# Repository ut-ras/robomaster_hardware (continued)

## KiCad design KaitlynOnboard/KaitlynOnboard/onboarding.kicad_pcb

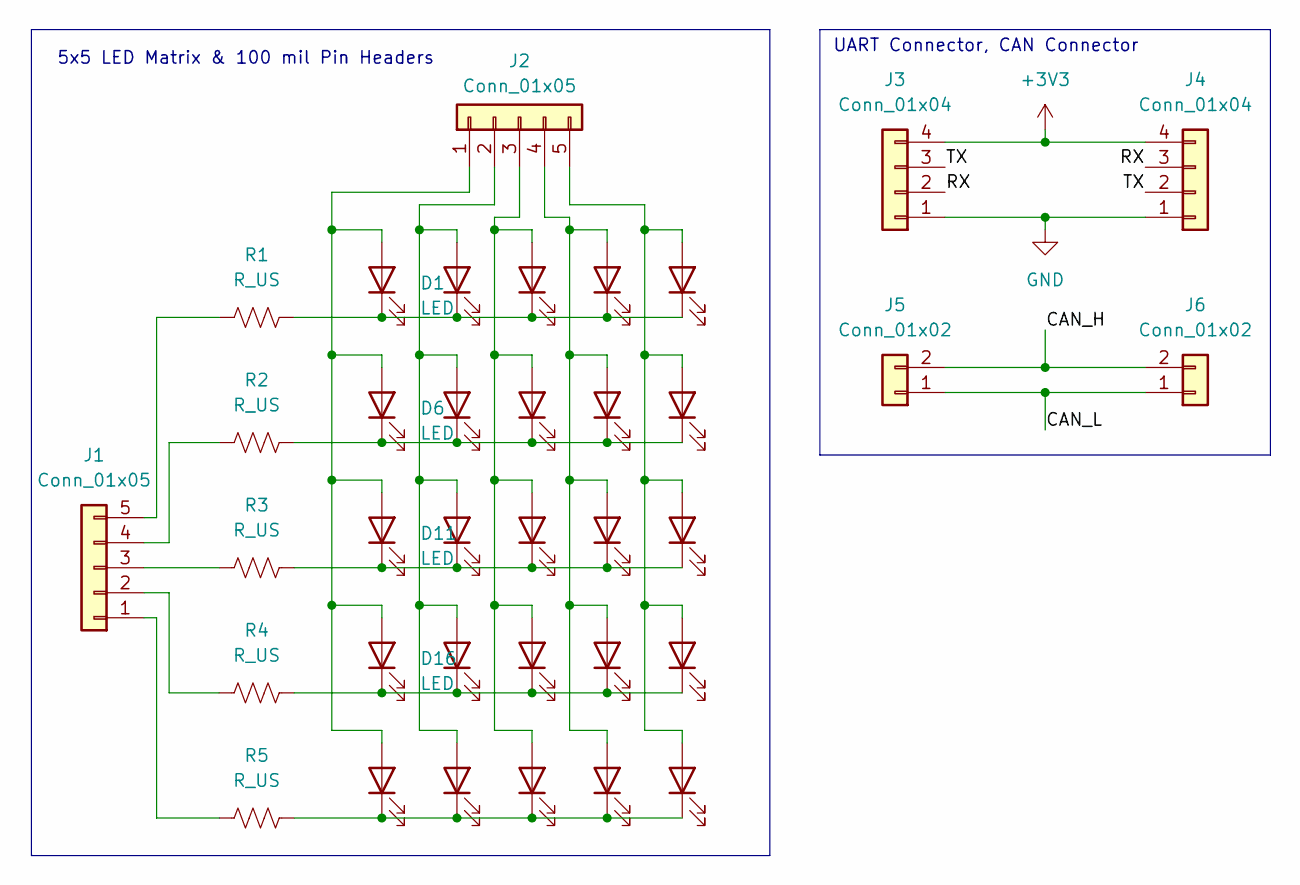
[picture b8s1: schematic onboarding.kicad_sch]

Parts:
D1, D2, D3, D4, D5, D6, D7, D8, D9, D10, D11, D12, D13, D14, D15, D16, D17, D18, D19, D20, D21, D22, D23, D24, D25: LED; LED_D3.0mm
J1, J2: Conn_01x05; PinHeader_1x05_P2.54mm_Vertical
J3, J4: Conn_01x04; JST_GH_BM04B-GHS-TBT_1x04-1MP_P1.25mm_Vertical
J5, J6: Conn_01x02; JST_GH_BM02B-GHS-TBT_1x02-1MP_P1.25mm_Vertical
R1, R2, R3, R4, R5: R_US; R_Axial_DIN0207_L6.3mm_D2.5mm_P7.62mm_Horizontal

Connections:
+3V3: J3.4, J4.4
/CAN_H: J5.2, J6.2
/CAN_L: J5.1, J6.1
/RX: J3.2, J4.3
/TX: J3.3, J4.2
GND: J3.1, J4.1
unnamed: D1.2 (A), D6.2 (A), D11.2 (A), D16.2 (A), D21.2 (A), J2.1
unnamed: D1.1 (K), D2.1 (K), D3.1 (K), D4.1 (K), D5.1 (K), R1.2
unnamed: D5.2 (A), D10.2 (A), D15.2 (A), D20.2 (A), D25.2 (A), J2.5
unnamed: D6.1 (K), D7.1 (K), D8.1 (K), D9.1 (K), D10.1 (K), R2.2
unnamed: D11.1 (K), D12.1 (K), D13.1 (K), D14.1 (K), D15.1 (K), R3.2
unnamed: D2.2 (A), D7.2 (A), D12.2 (A), D17.2 (A), D22.2 (A), J2.2
unnamed: D3.2 (A), D8.2 (A), D13.2 (A), D18.2 (A), D23.2 (A), J2.3
unnamed: D4.2 (A), D9.2 (A), D14.2 (A), D19.2 (A), D24.2 (A), J2.4
unnamed: D16.1 (K), D17.1 (K), D18.1 (K), D19.1 (K), D20.1 (K), R4.2
unnamed: D21.1 (K), D22.1 (K), D23.1 (K), D24.1 (K), D25.1 (K), R5.2
unnamed: J1.1, R5.1
unnamed: J1.2, R4.1
unnamed: J1.3, R3.1
unnamed: J1.4, R2.1
unnamed: J1.5, R1.1

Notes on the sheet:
UART Connector, CAN Connector
5x5 LED Matrix & 100 mil Pin Headers

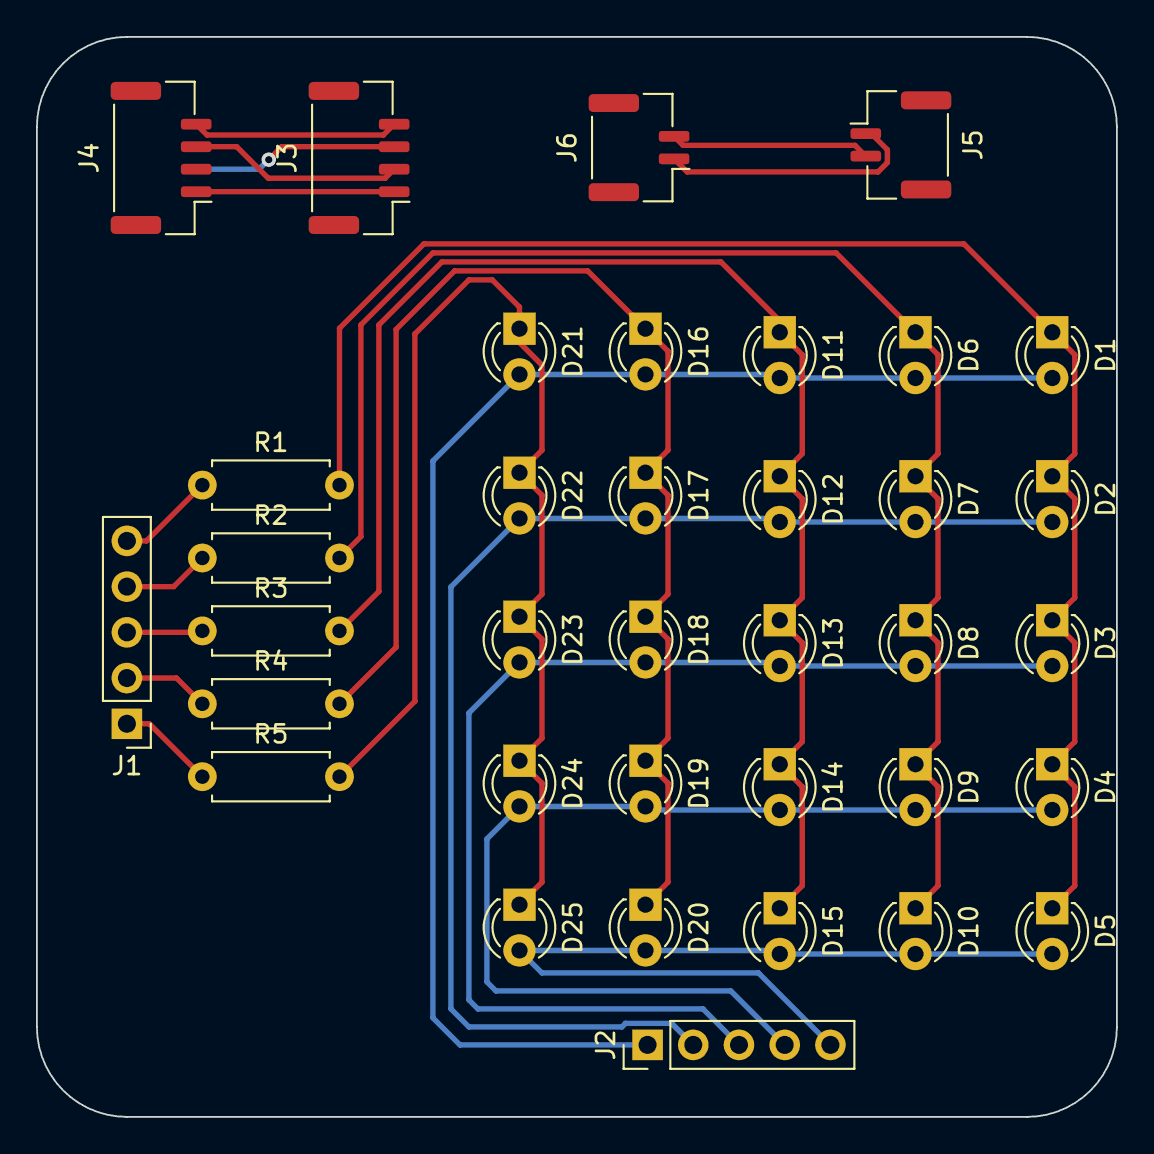
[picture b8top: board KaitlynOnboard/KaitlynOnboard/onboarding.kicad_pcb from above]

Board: 2 copper layers, 60.0 x 60.0 mm, 36 parts (0 on the bottom side), 21 nets.

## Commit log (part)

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2023-09-15 Create a .gitignore for the Chassis project
2023-09-17 Added submodule for Kicad and set libraries
2023-09-17 removed RM library
2023-09-22 Added all connectors + assigned footprints + created PCB file
    Starting layout now
2023-09-23 Change polarity of pins + add circular trace
2023-09-24 Routed CAN lines + made hole octagonal
    + differential pair skew fixed
    Dimensions may be subject to change, will have to redimension and reroute
2023-09-24 Possible indicator method?
2023-09-29 add Turret
2023-09-29 Add gitignore
2023-09-29 Lakshay's method
    I disagree
2023-09-29 Update schematic
2023-09-29 Add pcb
2023-09-30 schematic for dev board
2023-10-14 Added Resistor and LED footprints to schematic
2023-10-14 Wired to connector
2023-10-20 Remove snark
2023-10-21 added power connector
2023-10-22 Completed initial layout
    I'm going to get roasted over some of these choices
2023-10-22 Rearrange parts
2023-10-22 Updated step file
2023-10-22 Add/update READMEs
2023-10-22 Add big boy connector
2023-10-22 Update submodule reference
2023-10-27 Add power connector
    big boy
2023-10-27 Update .STEP file
2023-10-28 Update turret
2023-11-03 Added mounting holes
2023-11-04 Updated PCB to use unified power 6 pin, added 2 1x2 connectors
2023-11-04 Added pour for output
    Will need to add +5V buck + data connector + new power connector
    AAAAAAAAAAAAAAAAAAAAAAA
2023-11-11 Add box to schematic
2023-11-11 reset
2023-11-17 +5V buck
2023-11-18 Pass DRC
2023-11-18 Adjust silkscreen
2023-11-18 Reposition
2023-11-18 Straightened some kinks
2023-11-18 Add random microfit connector
    For data outputs
2023-11-18 Pass JLC DRC
2023-11-18 Mostly finished turret schematic
2023-11-18 Fixed 24V on sabre connector
2023-12-02 began adding traces :p
2023-12-19 Added test points + part number for diode
2023-12-19 update library
2023-12-20 turret dimensions
2024-01-04 Remove unnecessary holes + made some thermal vias into direct pours
2024-01-05 Clear PCB
    Rerouting hajimaruyo
2024-01-06 Much more pleasant dimensions
2024-01-07 Lots of placements
    Big blocks done, time to shuffle them around until I'm happy + route them
    4-layer board in the future?
2024-01-16 Did minor routing
2024-01-20 Winter Break Changes
2024-01-20 added mnfr numbers
2024-01-20 Finished routing
    Turns out we don't need the +5V buck kek
2024-01-27 added gimble power & motor connectors
2024-01-27 Turret change :)
2024-01-27 fixed sizing issues and added diodes
2024-01-27 some things
2024-02-01 Add .STEP file
2024-02-02 Resizing again :D
2024-02-03 made 80x80 & changed to 8 pin connector
2024-02-03 didn't really make any changes b/c of meetings but the board might be too long and I will add connectors to the diodes next time
2024-02-09 02/09/2024 sch
2024-02-10 Changed location of connectors of I2C and added mounting holes. Also I'm currently adding pads for the diodes
2024-02-10 Add files via upload
    WIRES
2024-02-17 Correct voltages
2024-02-17 added power sources
2024-02-17 fixed more sizing issues and I added a 1x4 connector to the data pins
2024-02-23 Fix CAN and change schematic
2024-02-24 Initial layout of footprints on pcb (not final)
2024-02-24 Moved stuff around
    yeah
2024-03-02 layout done need to do ref system
2024-03-02 Adding new ref system, other push now deprecated
2024-03-02 currently fixing footprints and aligned components
2024-03-06 New layout, test points not final
2024-03-06 finishing touches!
2024-03-07 Cleaned up silkscreen
    Went ham ngl
    Also passes all DRC checks
2024-03-08 Added connections to test points, silkscreens need to be renamed.
2024-03-08 J12 silkscreen names
2024-03-09 Hopefully Final DevBoard. I flipped the data connectors and fixed label placement
2024-03-09 forgot to add mounting holes
2024-03-09 Update silkscreen + address Lakshay's concerns
2024-03-09 Tried to fix footprints, also changed to traces for testpoints
2024-03-09 Add another pour
2024-03-18 Update wiring diagram with new proposal
2024-03-18 Create render action
    Getting a little bit silly with automatic rendering so you don't have to open VSCode every time you want to edit this
2024-03-18 Explicit file path
    Should latch onto the file in question now
2024-03-18 Update render.yml
    last try
2024-03-18 Automatically render .drawio files
2024-03-18 Update libraries & changed footprints
2024-03-22 added can2
2024-03-22 Adjust thingamajigs
    2nd CAN, silkscreen
2024-03-22 Adj silk
2024-03-22 Add le pikja
2024-03-22 New CAN Line, cleaned up schematic, changed pcb
2024-03-22 BOMs away
2024-03-23 fixed the tracks and pin headers and I only added diodes to the 3.3V pins
2024-03-23 Change output filtering for the +19V to 0805 (Mouser doesn't have 0603)
2024-03-23 Update footprints + pass DRC
2024-03-23 Add HSS
2024-03-23 Finish watchdog schematic
    idk if it works lol
2024-03-23 Fix power protection + adj silk
2024-03-24 Update and generate IBOM
2024-03-24 Added gerber & drill files, and zip for them
2024-03-24 Rename "plots" to "gerbers"
2024-03-26 Added 3d model
2024-03-29 Changed symbol fields
2024-03-29 added bom
2024-03-29 Add BOM (part 2)
2024-04-01 YEAH
2024-04-01 TEST TO MAKES REU
2024-04-01 just to make sure i don't explode
2024-04-01 UPDATE KICAD LIBRARY TO LATEST COMMIT
2024-04-02 Update README.md
    with Mouser BOM
2024-04-02 Update README.md
    make footer a note
2024-04-27 Assembled all passives
2024-08-14 Update pdf-diff.yml
    PR test
2024-08-14 Update pdf-diff.yml
    to allow for testing
2024-08-14 Update pdf-diff.yml
    upload artifacts => artifact
2024-08-14 Update pdf-diff.yml
    make ${{ github.workspace }}/ explicit
2024-08-14 Update pdf-diff.yml
    copy paste error
2024-08-14 Update pdf-diff.yml
    spel
2024-09-06 Did onboarding!
2024-09-13 Added name to READEME
2024-09-13 finished onboarding edit of readme
2024-09-13 As per Morris's instructions, adding a file with my personal information
2024-09-13 BryanQu test
2024-09-13 raeesahi
2024-09-13 sanjanahai
2024-09-13 message
2024-09-13 i approve of this message
2024-09-13 Hellow World!
2024-09-13 hi :}
2024-09-13 this is a test
2024-09-17 Reorganized chassis, turret, devboard shield, into monorepo
2024-09-17 Renamed directories to match
2024-09-17 Actually change Turret dir name?
2024-09-17 Renamed to Turret directory
2024-09-27 i hope this work
2024-09-27 pls work
2024-09-27 nithinBoarded
2024-09-29 Create SiddharthDtxt
2024-09-29 Update SiddharthDtxt
    Hello!
2024-09-30 New onboarding example
2024-10-01 Create JeffreyK
2024-10-04 added Egan Wang onboarding
2024-10-04 Add files via upload
    Ron Shemmer LED Matrix files
2024-10-04 Andrew onboarding
2024-10-09 new onboarding
2024-10-11 added first set of stuff for electrical diagram
2024-10-11 kicad for armorplate
2024-10-14 Updated ArmorPlate project dir name to be consistent
2024-10-14 onboarding
2024-10-15 Removed extra dir
2024-10-15 Moved some files around
2024-10-18 Prepped Electrical Diagram for meeting
2024-10-18 Initial commit
    Creating project files
2024-10-18 Add schematic page properties
2024-10-20 Added some text in the subsheets to outline what needs to be added inside of each subsheet
2024-10-21 Added two more subsheets and updated all text inside
2024-10-25 Add note about synchronous boost/buck needed
2024-11-09 please work
2024-11-11 Andrew added hierarchical labels to in/out pins on schematic
2024-11-16 added connections for chassis power to supercap
2024-11-16 Completed first version of housekeeping supplies
    +5V and +3V3 from mini PC +24V
2024-11-16 Adjust documentation
2024-11-17 Add encoder board
2024-11-18 Add switch for CW/CCW control
2024-11-23 Added hierarchical labels to ground pins in chassis
2024-11-23 added hierarchial labels for input/output characteristics
2024-11-23 added supercap connection
2024-11-23 Selected components for ideal diode and DACs
2024-11-24 Trying to do current sense but it's not fun
    canercanercnarennc
2024-11-29 Cleaned up hierarchical labels
2024-12-03 Prepped turret sch for 2x8 molex monolithic conn change
2024-12-07 Added hierarchial labels to chassis board, please look over
2024-12-07 separated grounds of powers
2024-12-07 Finish Dev board interface
    sorry morris
2024-12-07 flip
2024-12-07 Fix ground references
2024-12-07 last formatting change I promise
2024-12-07 Update library + update symbols
2024-12-07 Updating symbol library + passing some ERC tests
2024-12-07 Remove previous version of current sense
2024-12-07 Add in voltage control for components
2024-12-07 Added proper peripherals to ideal diode controller
    also updated library
2024-12-08 Finishing buck charger
2024-12-08 Define feedback networks
2024-12-08 Finish up buck
2024-12-08 attempting to fix comparators
    + global routing
2024-12-08 Reannotated
2024-12-15 Adding new DC DC converter IC
2024-12-15 Complete redesign of housekeeping supplies
    Attached picture is for the design of the housekeeping supplies
2025-01-08 Added a 16 input connector
2025-01-27 XT30 outputs to ESCs rotated
2025-01-27 Renamed project files for consistency
2025-01-31 Changed out floating ground connection to its proper counterpart
2025-01-31 Ideating for diff amp
2025-02-01 Created new folder for SPICE simulations, created SPICE simulation for ideal diode controller
2025-02-01 Moving around things
2025-02-03 Finalized Chassis Board
2025-02-07 Added blank project
2025-02-07 Created blank project and added kicad lib changes
2025-02-07 Moved dirs
2025-02-08 not sure :sparkle:
2025-02-08 updated schematic using sp3t switch
2025-02-12 Updated sheet dates & added new subsheets for parts I forgot to include
2025-02-12 Normally open => closed
2025-02-14 Onboarding for Sarthak Sarans
2025-02-15 updated pcb footprint for armorplate
2025-02-15 Replaced buck converter for 3V3, 3V3A, 5V with AZ34063U
2025-02-15 final armorplate pcb with sp3t toggle switch
2025-02-15 Added -3V3
2025-02-15 Added schematic for first stage of boost converter
2025-02-19 Added connector and updated kicad lib
2025-02-21 Updated electrical diagram and Kicad library
2025-02-21 Fixed 16-pin and 8-pin netnames for correct connections, updated gerbers
2025-02-21 Fixed hierachical labels for functionality, naming needs to be changed
2025-02-21 Staged hierarchical changes for chassis, not finished
2025-02-21 fabrication files for armorplate
2025-02-21 gerbfileszip
2025-02-22 started safety discharge
2025-02-22 Changed boost2
2025-02-22 Added starting files for sentry chassis
2025-02-22 Added hierarchical labels
2025-02-22 Updated AND gate input circuits, added specs to diodes
2025-02-22 Replaced opamp with better one
2025-02-28 Update boost 2
2025-03-01 Changed to GNDPWR for -3V3 step-down converter
2025-03-01 Redesigned stage 1 converter for clarity
2025-03-01 sumbission for Neil
2025-03-01 Reduced link size, added buck converter calculations excel sheet
2025-03-07 new boost 2 schematic
2025-03-07 Added hierarchical outputs to chassis grounds
2025-03-07 staging before meeting
2025-03-08 Flip MOSFET for ideal diode controller
2025-03-08 Added internal connection for ref ports and distiniguished i/o
2025-03-08 Switched over to TI buck conveter
2025-03-08 To simulate buck, replace 22u with {L2} and 100u with {C3}
2025-03-08 Update .gitignore for LTSpice files
2025-03-17 Update current sense comparator resistor values
2025-03-20 Simulated + designed current sense circuitry
2025-03-20 Remove flavor text for validation
2025-03-20 Update simulations to match current sensor design
2025-03-20 Updated fab files
2025-03-21 Adjust housekeeping power supplies to remove output filter network
2025-03-21 Remove unnecessary files
    DON'T COMMIT THESE HUGE FILES TO GIT IN THE FUTURE!!!
2025-03-21 Renumber components
2025-03-21 Various mouser part changes
